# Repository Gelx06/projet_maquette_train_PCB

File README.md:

# ** Projet_maquette_train_PCB **
Moderniser une maquette de train utilisé en S2 pour l'initialisation à l'IE pour les BUT1 et BUT2.

Réalisé par Angelo PIERRE LOUIS

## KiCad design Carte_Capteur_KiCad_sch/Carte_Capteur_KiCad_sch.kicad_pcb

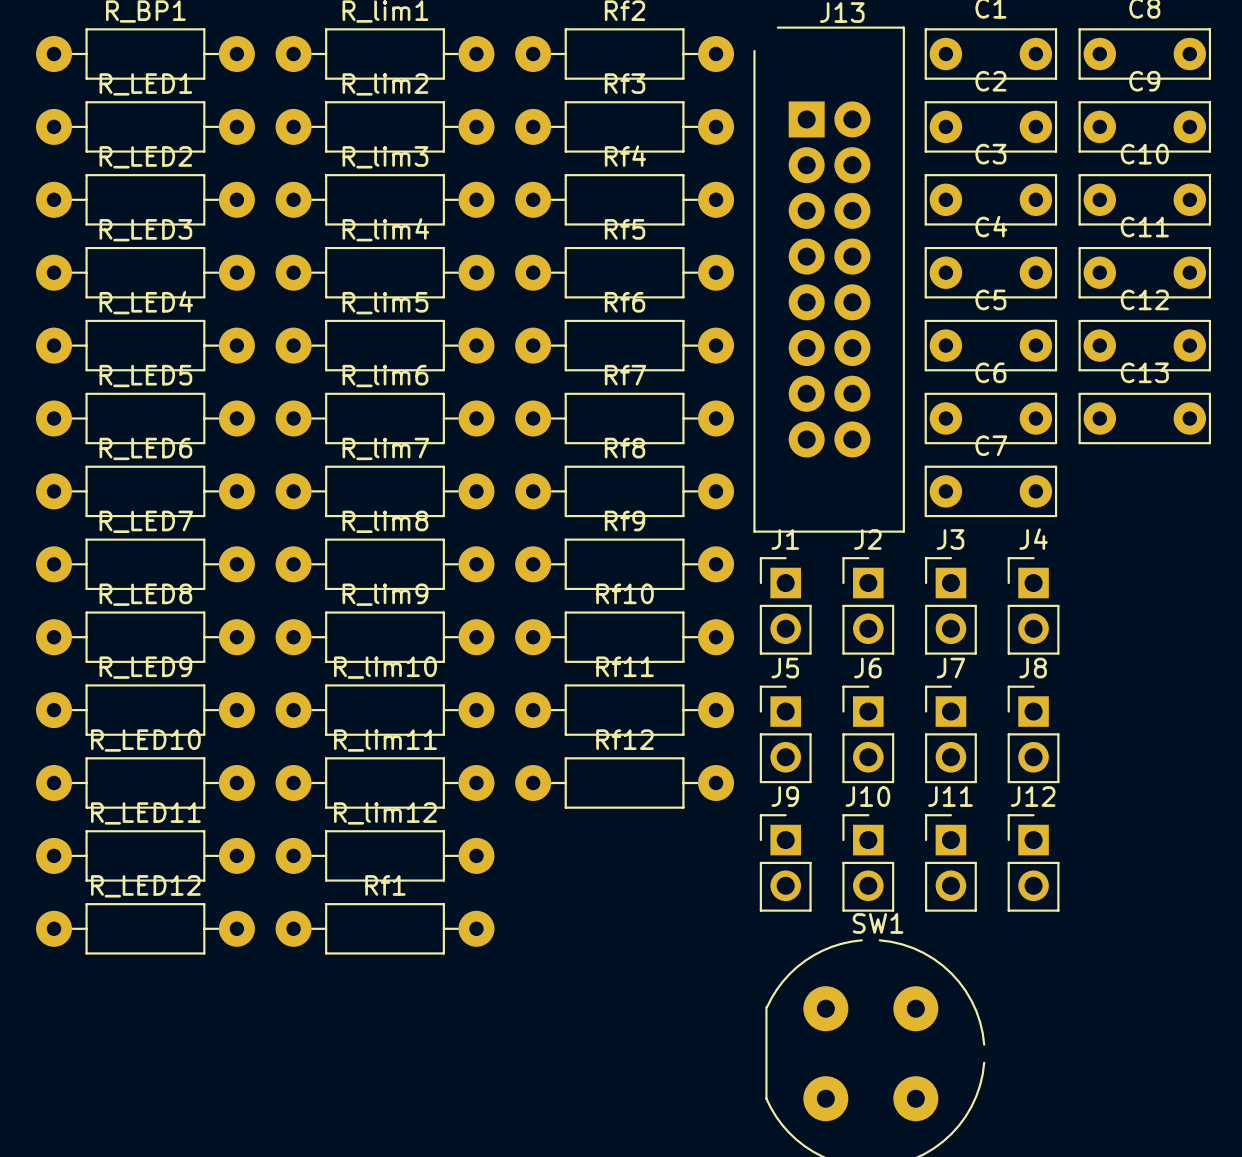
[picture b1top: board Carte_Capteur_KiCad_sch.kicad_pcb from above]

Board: 2 copper layers, 64 parts (0 on the bottom side), 39 nets, no tracks yet.

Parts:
C1, C2, C3, C4, C5, C6, C7, C8, C9, C10, C11, C12, C13: 100nF; C_Rect_L7.0mm_W2.5mm_P5.00mm
J1, J2, J3, J4, J5, J6, J7, J8, J9, J10, J11, J12: J_capteur; PinHeader_1x02_P2.54mm_Vertical
J13: HE10_02x08; HE10_2x08_P2.54mm
R_BP1: 10k; R_Axial_DIN0207_L6.3mm_D2.5mm_P10.16mm_Horizontal
R_LED1, R_LED2, R_LED3, R_LED4, R_LED5, R_LED6, R_LED7, R_LED8, R_LED9, R_LED10, R_LED11, R_LED12: 1k; R_Axial_DIN0207_L6.3mm_D2.5mm_P10.16mm_Horizontal
R_lim1, R_lim2, R_lim3, R_lim4, R_lim5, R_lim6, R_lim7, R_lim8, R_lim9, R_lim10, R_lim11, R_lim12: 1k; R_Axial_DIN0207_L6.3mm_D2.5mm_P10.16mm_Horizontal
Rf1, Rf2, Rf3, Rf4, Rf5, Rf6, Rf7, Rf8, Rf9, Rf10, Rf11, Rf12: 10k; R_Axial_DIN0207_L6.3mm_D2.5mm_P10.16mm_Horizontal
SW1: SW_Push_blue; SW_PUSH_5mm_blue

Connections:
+3.3V: J1.1, J2.1, J3.1, J4.1, J5.1, J6.1, J7.1, J8.1, J9.1, J10.1, J11.1, J12.1, J13.15, SW1.2
/BP: C13.1, J13.13, R_BP1.1, SW1.1
/SIG_1: J13.1, R_LED12.1
/SIG_2: J13.2, R_LED1.1
/SIG_3: J13.3, R_LED2.1
/SIG_4: J13.4, R_LED3.1
/SIG_5: J13.5, R_LED4.1
/SIG_6: J13.6, R_LED5.1
/SIG_7: J13.7, R_LED6.1
/SIG_8: J13.8, R_LED7.1
/SIG_9: J13.9, R_LED8.1
/SIG_10: J13.10, R_LED9.1
/SIG_11: J13.11, R_LED10.1
/SIG_12: J13.12, R_LED11.1
GND: C1.2, C2.2, C3.2, C4.2, C5.2, C6.2, C7.2, C8.2, C9.2, C10.2, C11.2, C12.2, C13.2, J13.14, J13.16, R_BP1.2
unnamed: C1.1, Rf12.1
unnamed: C2.1, Rf1.1
unnamed: C3.1, Rf2.1
unnamed: C4.1, Rf3.1
unnamed: C5.1, Rf4.1
unnamed: C6.1, Rf5.1
unnamed: C7.1, Rf6.1
unnamed: C8.1, Rf7.1
unnamed: C9.1, Rf8.1
unnamed: C10.1, Rf9.1
unnamed: C11.1, Rf10.1
unnamed: C12.1, Rf11.1
unnamed: J1.2, R_lim12.1, Rf12.2
unnamed: J2.2, R_lim1.1, Rf1.2
unnamed: J3.2, R_lim2.1, Rf2.2
unnamed: J4.2, R_lim3.1, Rf3.2
unnamed: J5.2, R_lim4.1, Rf4.2
unnamed: J6.2, R_lim5.1, Rf5.2
unnamed: J7.2, R_lim6.1, Rf6.2
unnamed: J8.2, R_lim7.1, Rf7.2
unnamed: J9.2, R_lim8.1, Rf8.2
unnamed: J10.2, R_lim9.1, Rf9.2
unnamed: J11.2, R_lim10.1, Rf10.2
unnamed: J12.2, R_lim11.1, Rf11.2
